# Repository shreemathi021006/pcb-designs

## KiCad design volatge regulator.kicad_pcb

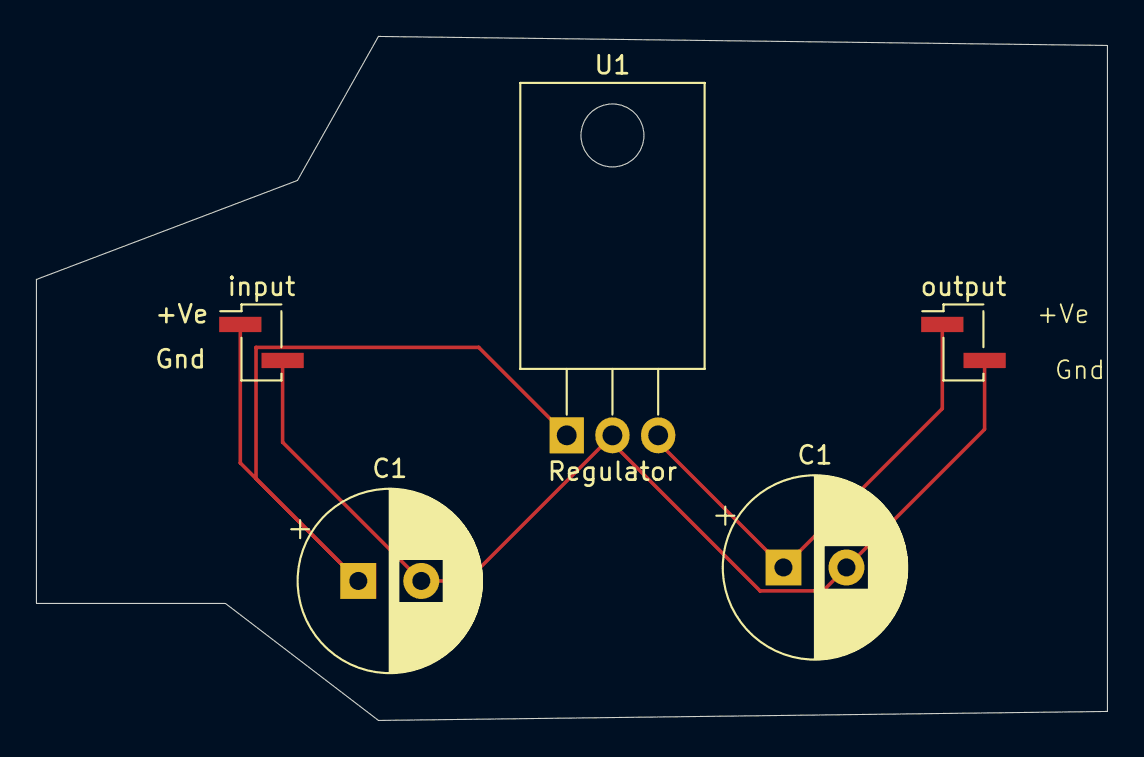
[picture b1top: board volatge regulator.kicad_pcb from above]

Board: 2 copper layers, 59.5 x 38.0 mm, 5 parts (0 on the bottom side), 3 nets.

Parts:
C1, C1#2: 0.33µF; CP_Radial_D10.0mm_P3.50mm
U1: Regulator; TO-220-3_Horizontal_TabDown
input: output; PinHeader_1x02_P2.00mm_Vertical_SMD_Pin1Left
output: Conn_01x02; PinHeader_1x02_P2.00mm_Vertical_SMD_Pin1Left

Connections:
unnamed: C1.1, U1.1 (IN), input.1
unnamed: C1.2, C1#2.2, U1.2 (GND), input.2, output.2
unnamed: C1#2.1, U1.3 (OUT), output.1

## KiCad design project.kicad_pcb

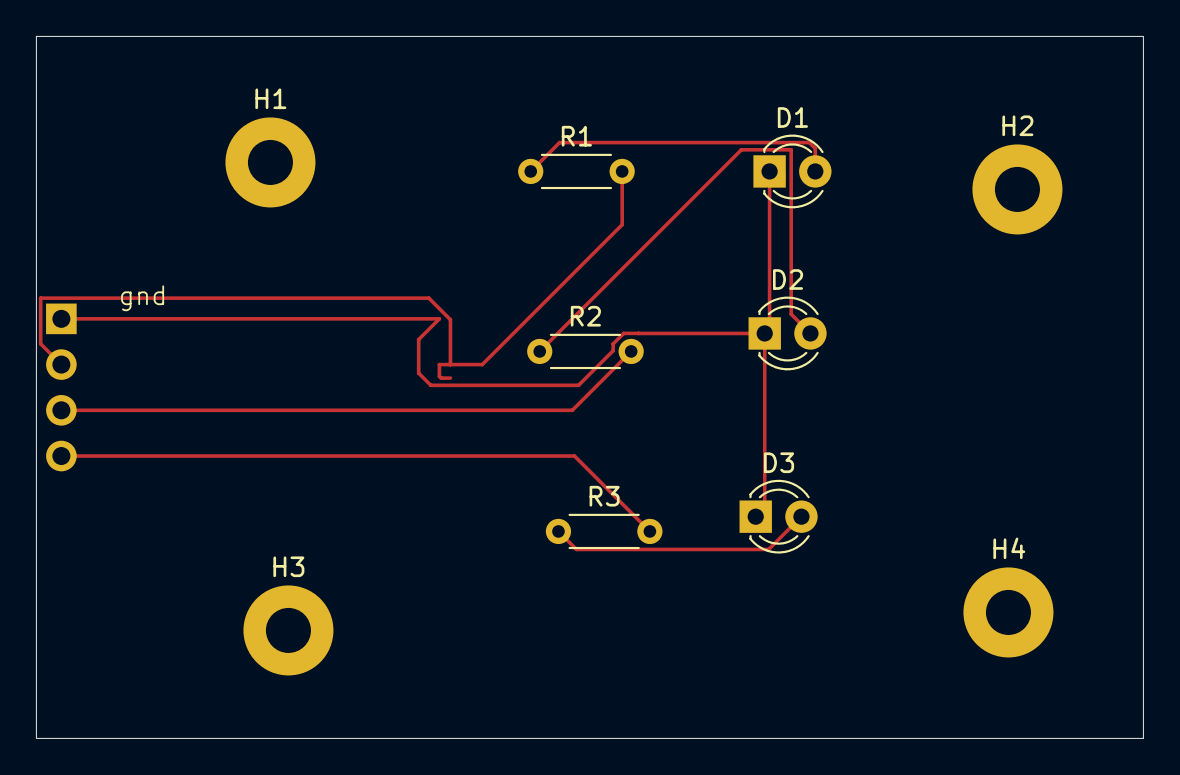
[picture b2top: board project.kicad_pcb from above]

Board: 2 copper layers, 61.5 x 39.0 mm, 11 parts (1 on the bottom side), 7 nets.

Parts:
D1, D2, D3: LED; LED_D3.0mm
H1, H2, H3, H4: MountingHole; MountingHole_2.5mm_Pad
J1: Conn_01x04_Pin; PinHeader_1x04_P2.54mm_Horizontal
R1, R2, R3: R; R_Axial_DIN0204_L3.6mm_D1.6mm_P5.08mm_Horizontal

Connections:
unnamed: D1.2 (A), R1.1
unnamed: D1.1 (K), D2.1 (K), D3.1 (K), J1.1
unnamed: D2.2 (A), R2.1
unnamed: D3.2 (A), R3.1
unnamed: J1.2, R1.2
unnamed: J1.3, R2.2
unnamed: J1.4, R3.2

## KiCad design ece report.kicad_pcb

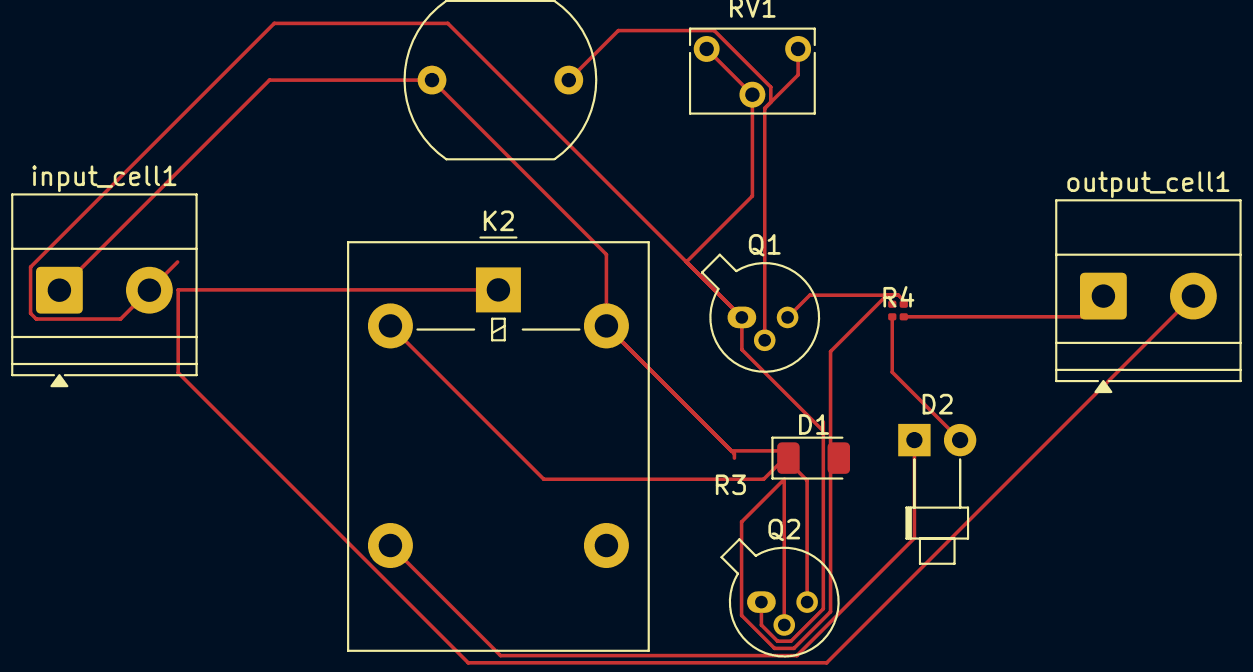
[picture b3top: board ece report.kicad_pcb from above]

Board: 2 copper layers, 11 parts (0 on the bottom side), 9 nets.

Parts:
D1: D; D_1206_3216Metric
D2: LED; LED_D1.8mm_W1.8mm_H2.4mm_Horizontal_O3.81mm_Z4.9mm
K2: G5LE-1; Relay_SPDT_Omron-G5LE-1
Q1, Q2: BC107; TO-18-3
R1: LDR03; R_LDR_10x8.5mm_P7.6mm_Vertical
R3: 1kΩ; R_0201_0603Metric
R4: R; R_0201_0603Metric
RV1: R_Potentiometer; Potentiometer_Bourns_3266W_Vertical
input_cell1: Conn_01x02_Pin; TerminalBlock_Phoenix_MKDS-1,5-2_1x02_P5.00mm_Horizontal
output_cell1: Conn_01x02_Pin; TerminalBlock_Phoenix_MKDS-1,5-2_1x02_P5.00mm_Horizontal

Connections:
unnamed: D1.2 (A), K2.2, Q2.3 (C)
unnamed: D1.1 (K), K2.5, R1.1, R3.1, input_cell1.1
unnamed: D2.2 (A), R4.1
unnamed: D2.1 (K), K2.3
unnamed: Q1.2 (B), R1.2, RV1.1
unnamed: Q1.3 (C), Q2.2 (B), R3.2
unnamed: Q1.1 (E), Q2.1 (E), RV1.2, RV1.3, input_cell1.2
unnamed: R4.2, output_cell1.1
unnamed: K2.1, output_cell1.2

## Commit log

2025-07-18 This gives the glimpse of pcb design that i made
    this pcb is basically for the automatic switching of lligh using ldr and relay
2025-07-18 The pcb design that i made first as practice
2025-07-18 Here i have added the file of the pcb design which i designed for voltage regulator
2025-07-26 Create Motor driver
    Have a look into my motor driver
2025-07-26 Create schematic pdfs
2025-07-26 Add files via upload
    Schematic of a automatic street light using ldr and relay
2025-07-26 Create README.md
    link to view the schematics
2025-07-26 Create Schematics link
    Link to see the schematic pdfs
2025-07-26 Update Schematics lilnk
2025-09-06 tried to add whole folders
2025-12-06 Update README.md
    Added a header for schematics and PCB designs section.
2025-12-06 Mini project
2025-12-06 Dual Motor driver
2025-12-06 wave form generator using ua741
